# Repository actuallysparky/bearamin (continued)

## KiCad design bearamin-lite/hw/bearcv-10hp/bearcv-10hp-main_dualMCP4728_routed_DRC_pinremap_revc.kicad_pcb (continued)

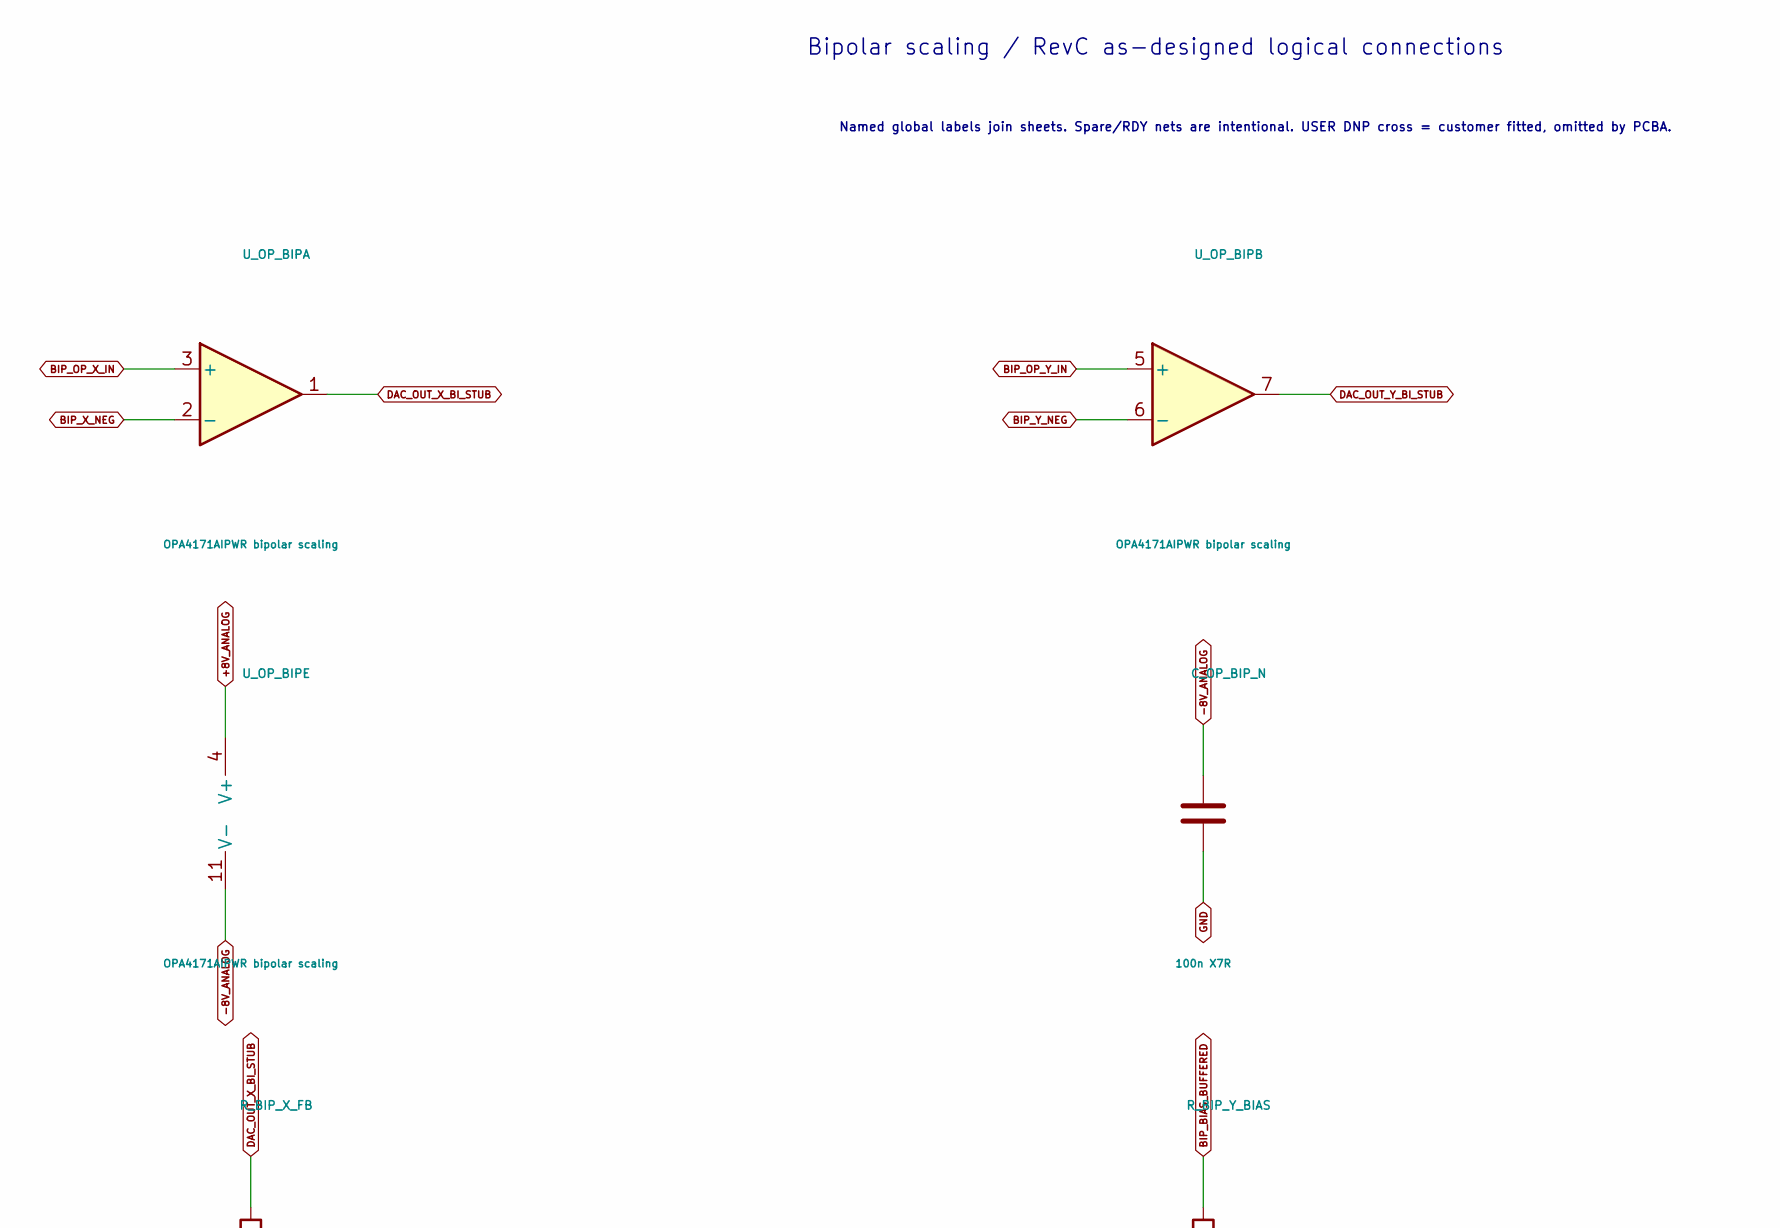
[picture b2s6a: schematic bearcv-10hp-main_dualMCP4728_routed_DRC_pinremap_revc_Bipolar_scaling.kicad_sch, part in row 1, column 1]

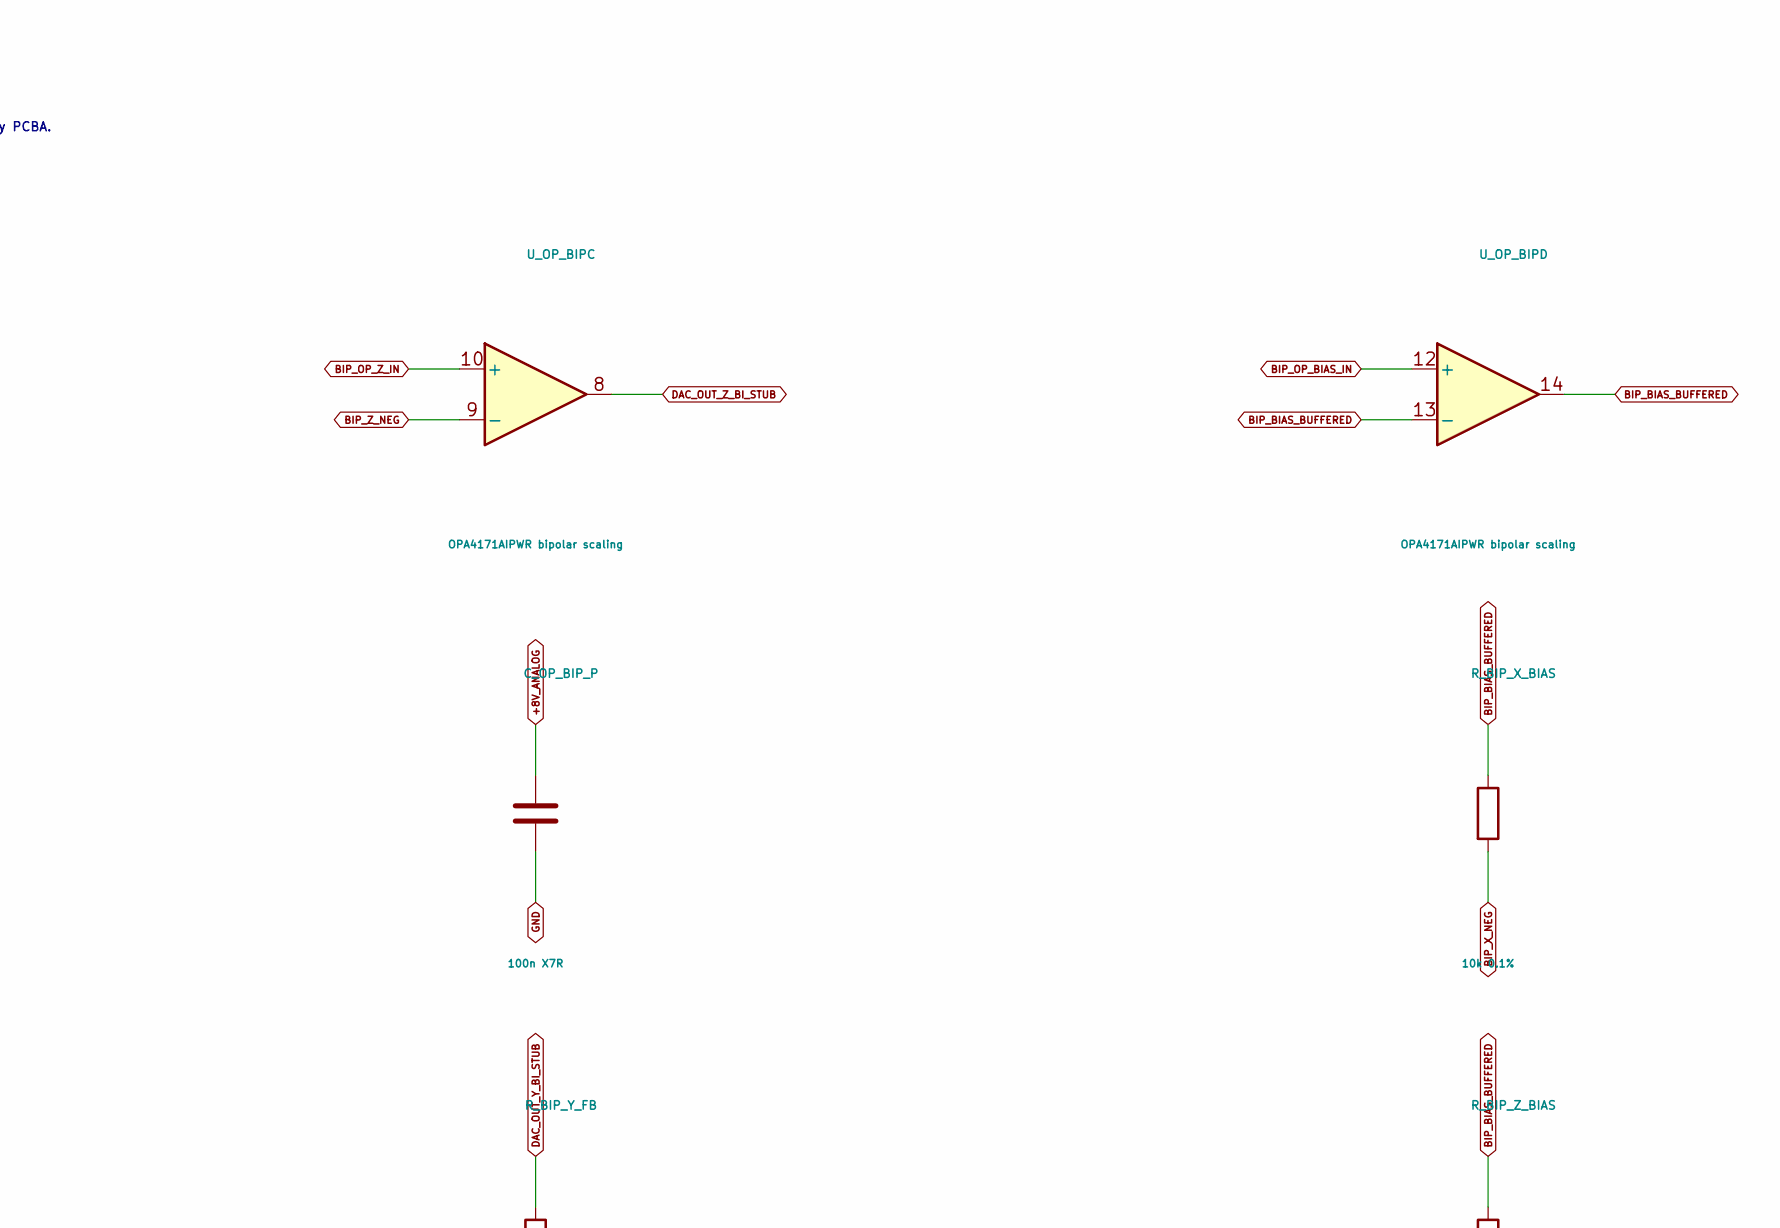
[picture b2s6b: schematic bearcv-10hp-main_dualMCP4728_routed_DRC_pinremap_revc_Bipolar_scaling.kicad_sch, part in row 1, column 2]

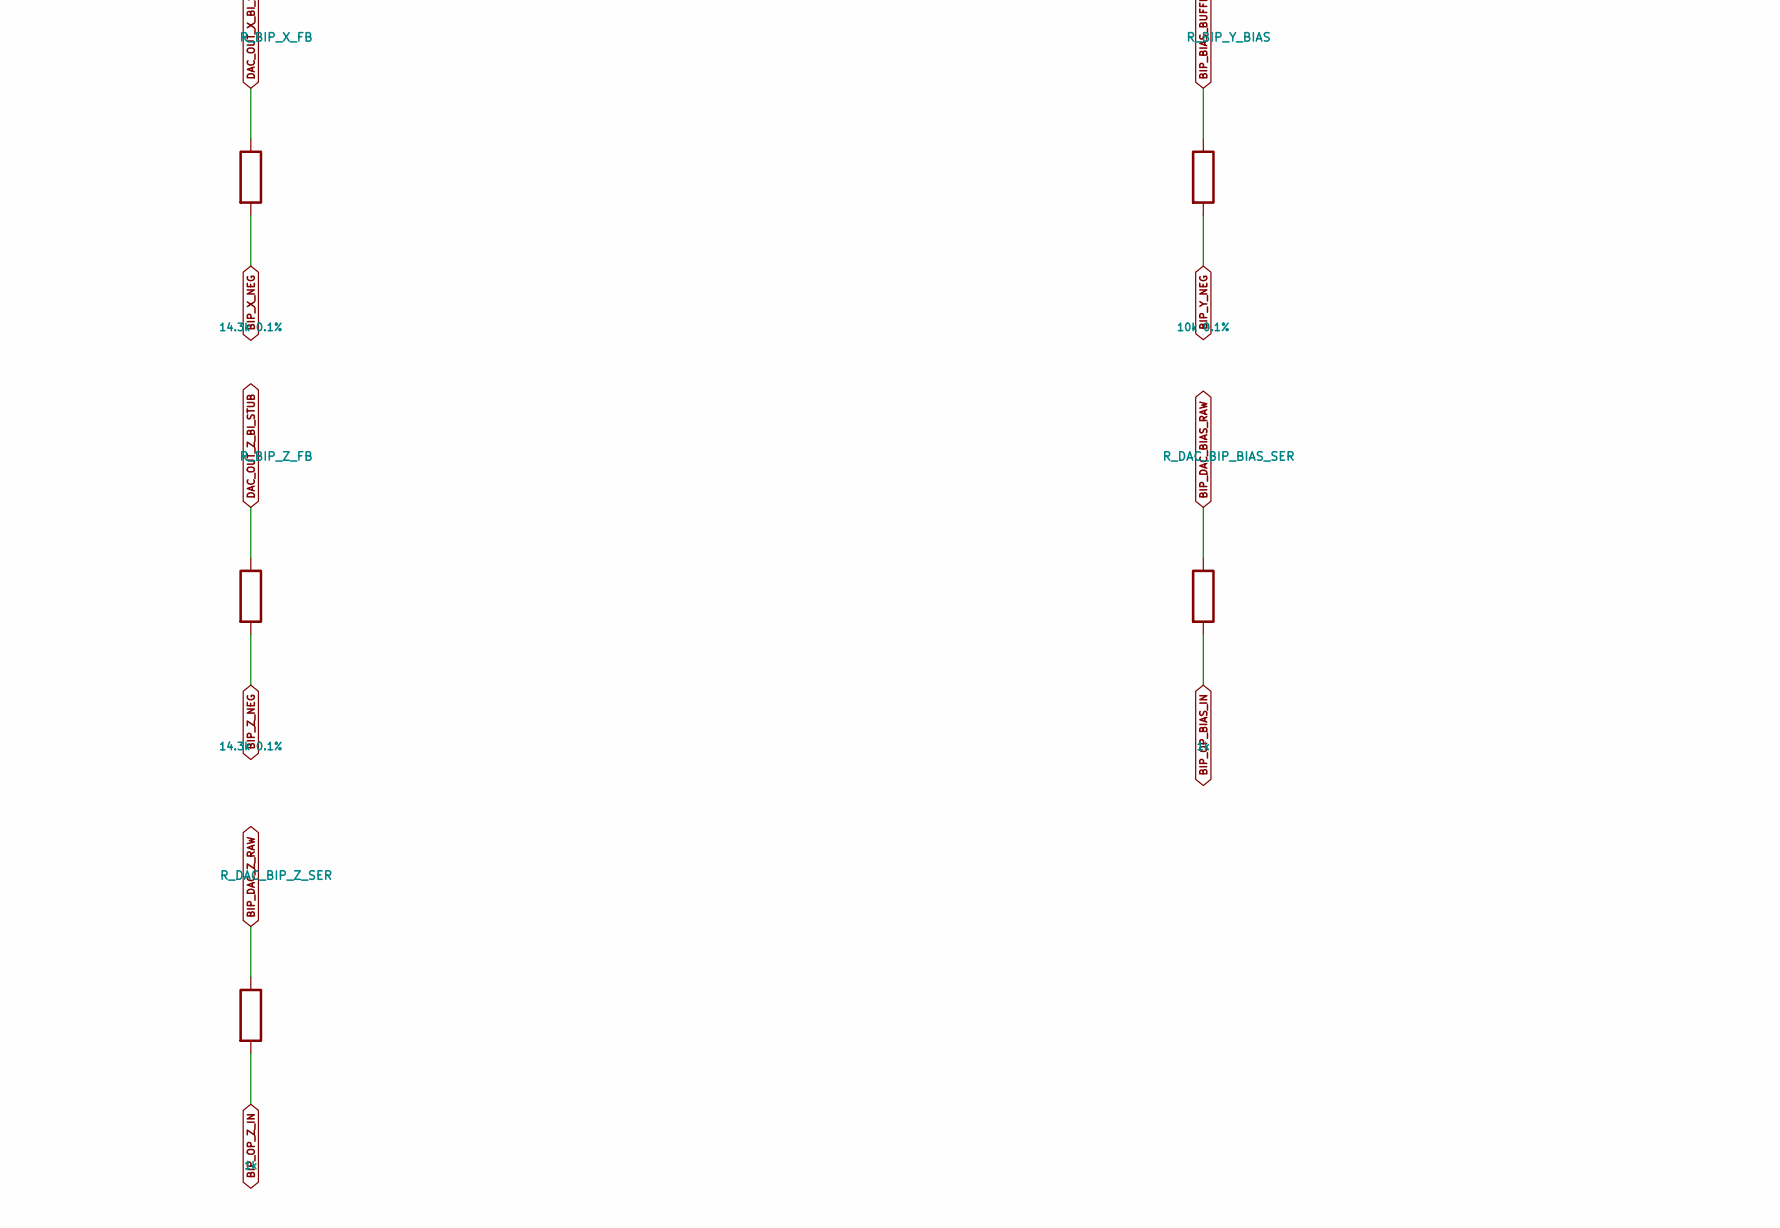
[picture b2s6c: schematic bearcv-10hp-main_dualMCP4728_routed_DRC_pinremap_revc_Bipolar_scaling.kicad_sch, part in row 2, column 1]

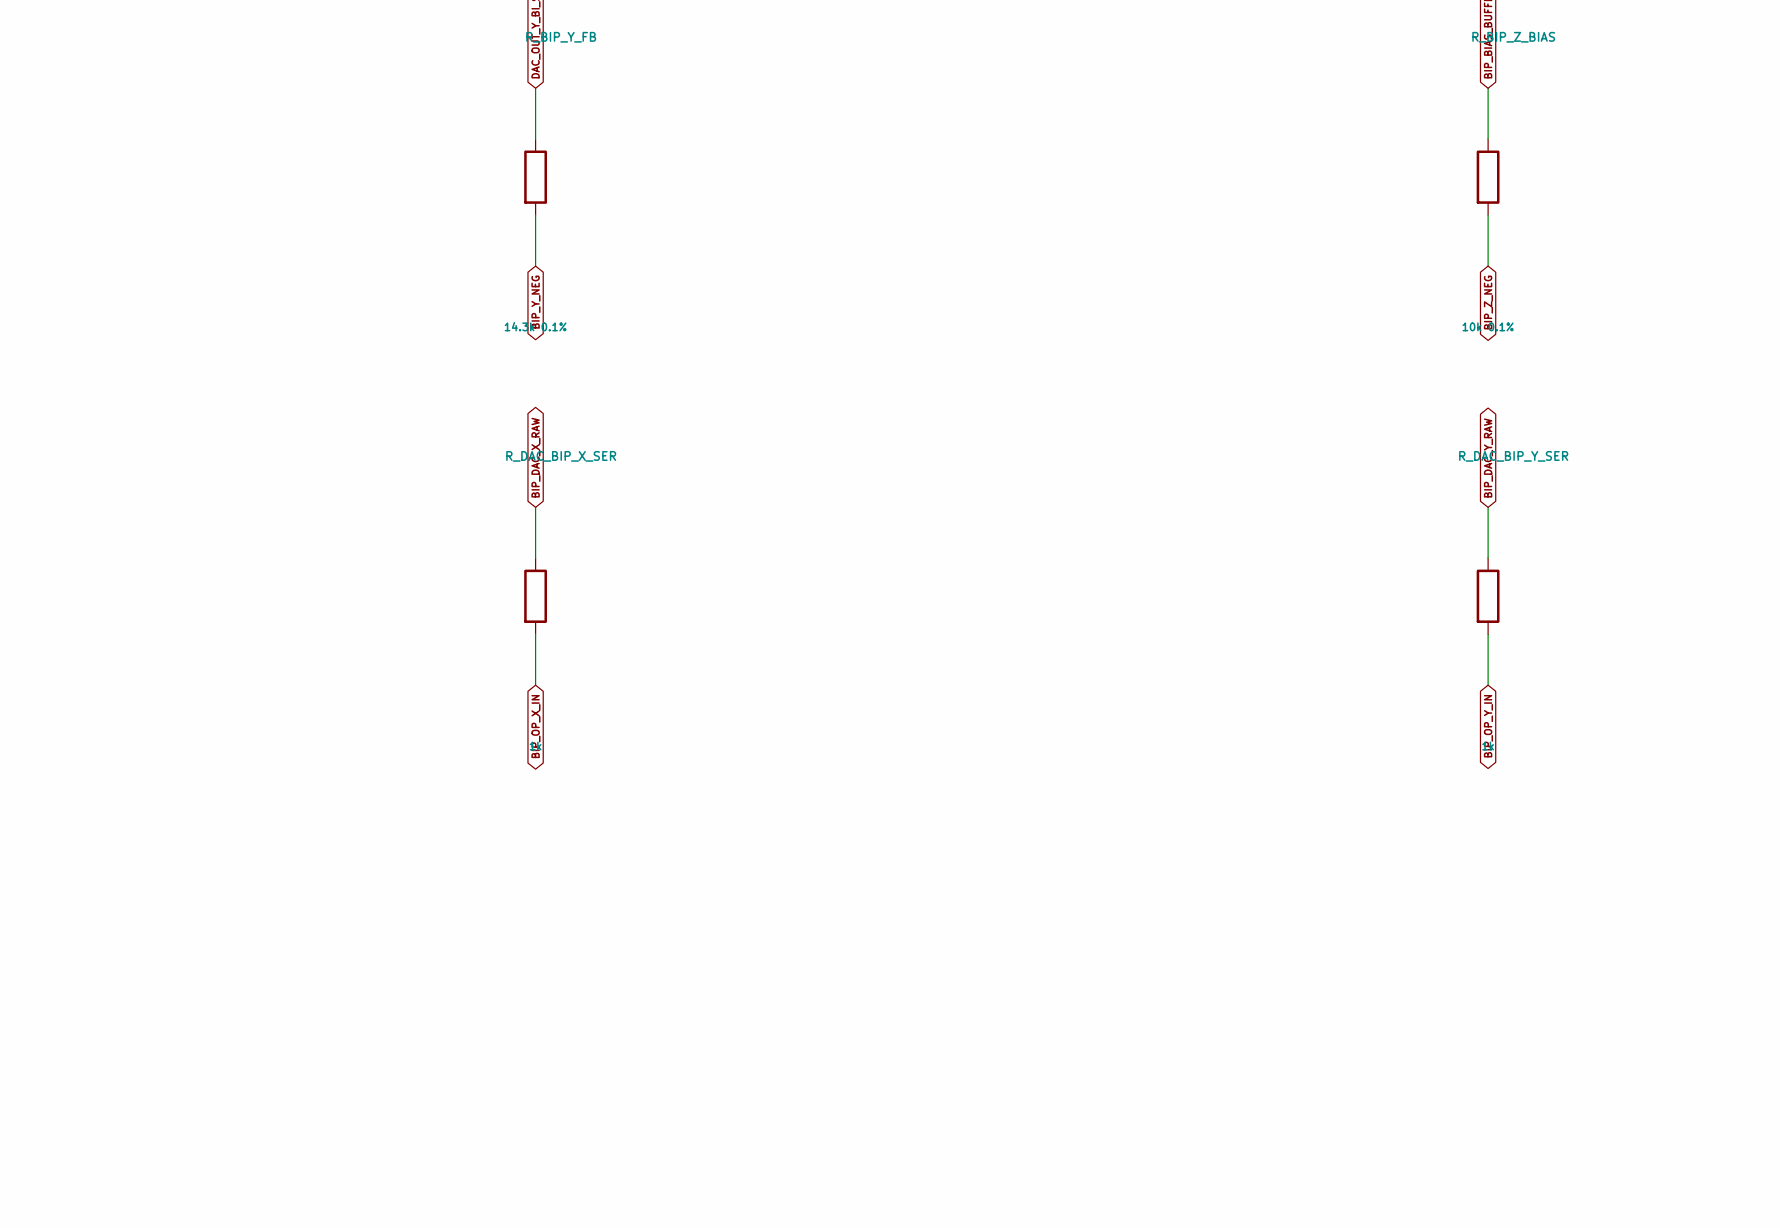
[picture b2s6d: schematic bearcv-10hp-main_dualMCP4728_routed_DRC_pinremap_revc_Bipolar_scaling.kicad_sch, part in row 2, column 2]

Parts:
C_OP_BIP_N: 100n X7R; MPN CC0603KRX7R9BB104; JLCPCB Part C14663
C_OP_BIP_P: 100n X7R; MPN CC0603KRX7R9BB104; JLCPCB Part C14663
R_BIP_X_BIAS: 10k 0.1%; MPN RT0603BRD0710KL; JLCPCB Library Extended
R_BIP_X_FB: 14.3k 0.1%; MPN RT0603BRE0714K3L; JLCPCB Library Extended
R_BIP_Y_BIAS: 10k 0.1%; MPN RT0603BRD0710KL; JLCPCB Library Extended
R_BIP_Y_FB: 14.3k 0.1%; MPN RT0603BRE0714K3L; JLCPCB Library Extended
R_BIP_Z_BIAS: 10k 0.1%; MPN RT0603BRD0710KL; JLCPCB Library Extended
R_BIP_Z_FB: 14.3k 0.1%; MPN RT0603BRE0714K3L; JLCPCB Library Extended
R_DAC_BIP_BIAS_SER: 1k; MPN 0603WAF1001T5E; JLCPCB Part C21190
R_DAC_BIP_X_SER: 1k; MPN 0603WAF1001T5E; JLCPCB Part C21190
R_DAC_BIP_Y_SER: 1k; MPN 0603WAF1001T5E; JLCPCB Part C21190
R_DAC_BIP_Z_SER: 1k; MPN 0603WAF1001T5E; JLCPCB Part C21190
U_OP_BIP: OPA4171AIPWR bipolar scaling; MPN OPA4171AIPWR; JLCPCB Part C529553

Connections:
+8V_ANALOG: C_OP_BIP_P.1, U_OP_BIP.4 (V+); also elsewhere on the board
-8V_ANALOG: C_OP_BIP_N.1, U_OP_BIP.11 (V-); also elsewhere on the board
BIP_BIAS_BUFFERED: R_BIP_X_BIAS.1, R_BIP_Y_BIAS.1, R_BIP_Z_BIAS.1, U_OP_BIP.13 (-), U_OP_BIP.14
BIP_DAC_BIAS_RAW: R_DAC_BIP_BIAS_SER.1; also elsewhere on the board
BIP_DAC_X_RAW: R_DAC_BIP_X_SER.1; also elsewhere on the board
BIP_DAC_Y_RAW: R_DAC_BIP_Y_SER.1; also elsewhere on the board
BIP_DAC_Z_RAW: R_DAC_BIP_Z_SER.1; also elsewhere on the board
BIP_OP_BIAS_IN: R_DAC_BIP_BIAS_SER.2, U_OP_BIP.12 (+)
BIP_OP_X_IN: R_DAC_BIP_X_SER.2, U_OP_BIP.3 (+)
BIP_OP_Y_IN: R_DAC_BIP_Y_SER.2, U_OP_BIP.5 (+)
BIP_OP_Z_IN: R_DAC_BIP_Z_SER.2, U_OP_BIP.10 (+)
BIP_X_NEG: R_BIP_X_BIAS.2, R_BIP_X_FB.2, U_OP_BIP.2 (-)
BIP_Y_NEG: R_BIP_Y_BIAS.2, R_BIP_Y_FB.2, U_OP_BIP.6 (-)
BIP_Z_NEG: R_BIP_Z_BIAS.2, R_BIP_Z_FB.2, U_OP_BIP.9 (-)
DAC_OUT_X_BI_STUB: R_BIP_X_FB.1, U_OP_BIP.1; also elsewhere on the board
DAC_OUT_Y_BI_STUB: R_BIP_Y_FB.1, U_OP_BIP.7; also elsewhere on the board
DAC_OUT_Z_BI_STUB: R_BIP_Z_FB.1, U_OP_BIP.8; also elsewhere on the board
GND: C_OP_BIP_N.2, C_OP_BIP_P.2; also elsewhere on the board

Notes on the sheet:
Bipolar scaling / RevC as-designed logical connections
Named global labels join sheets. Spare/RDY nets are intentional. USER DNP cross = customer fitted, omitted by PCBA.

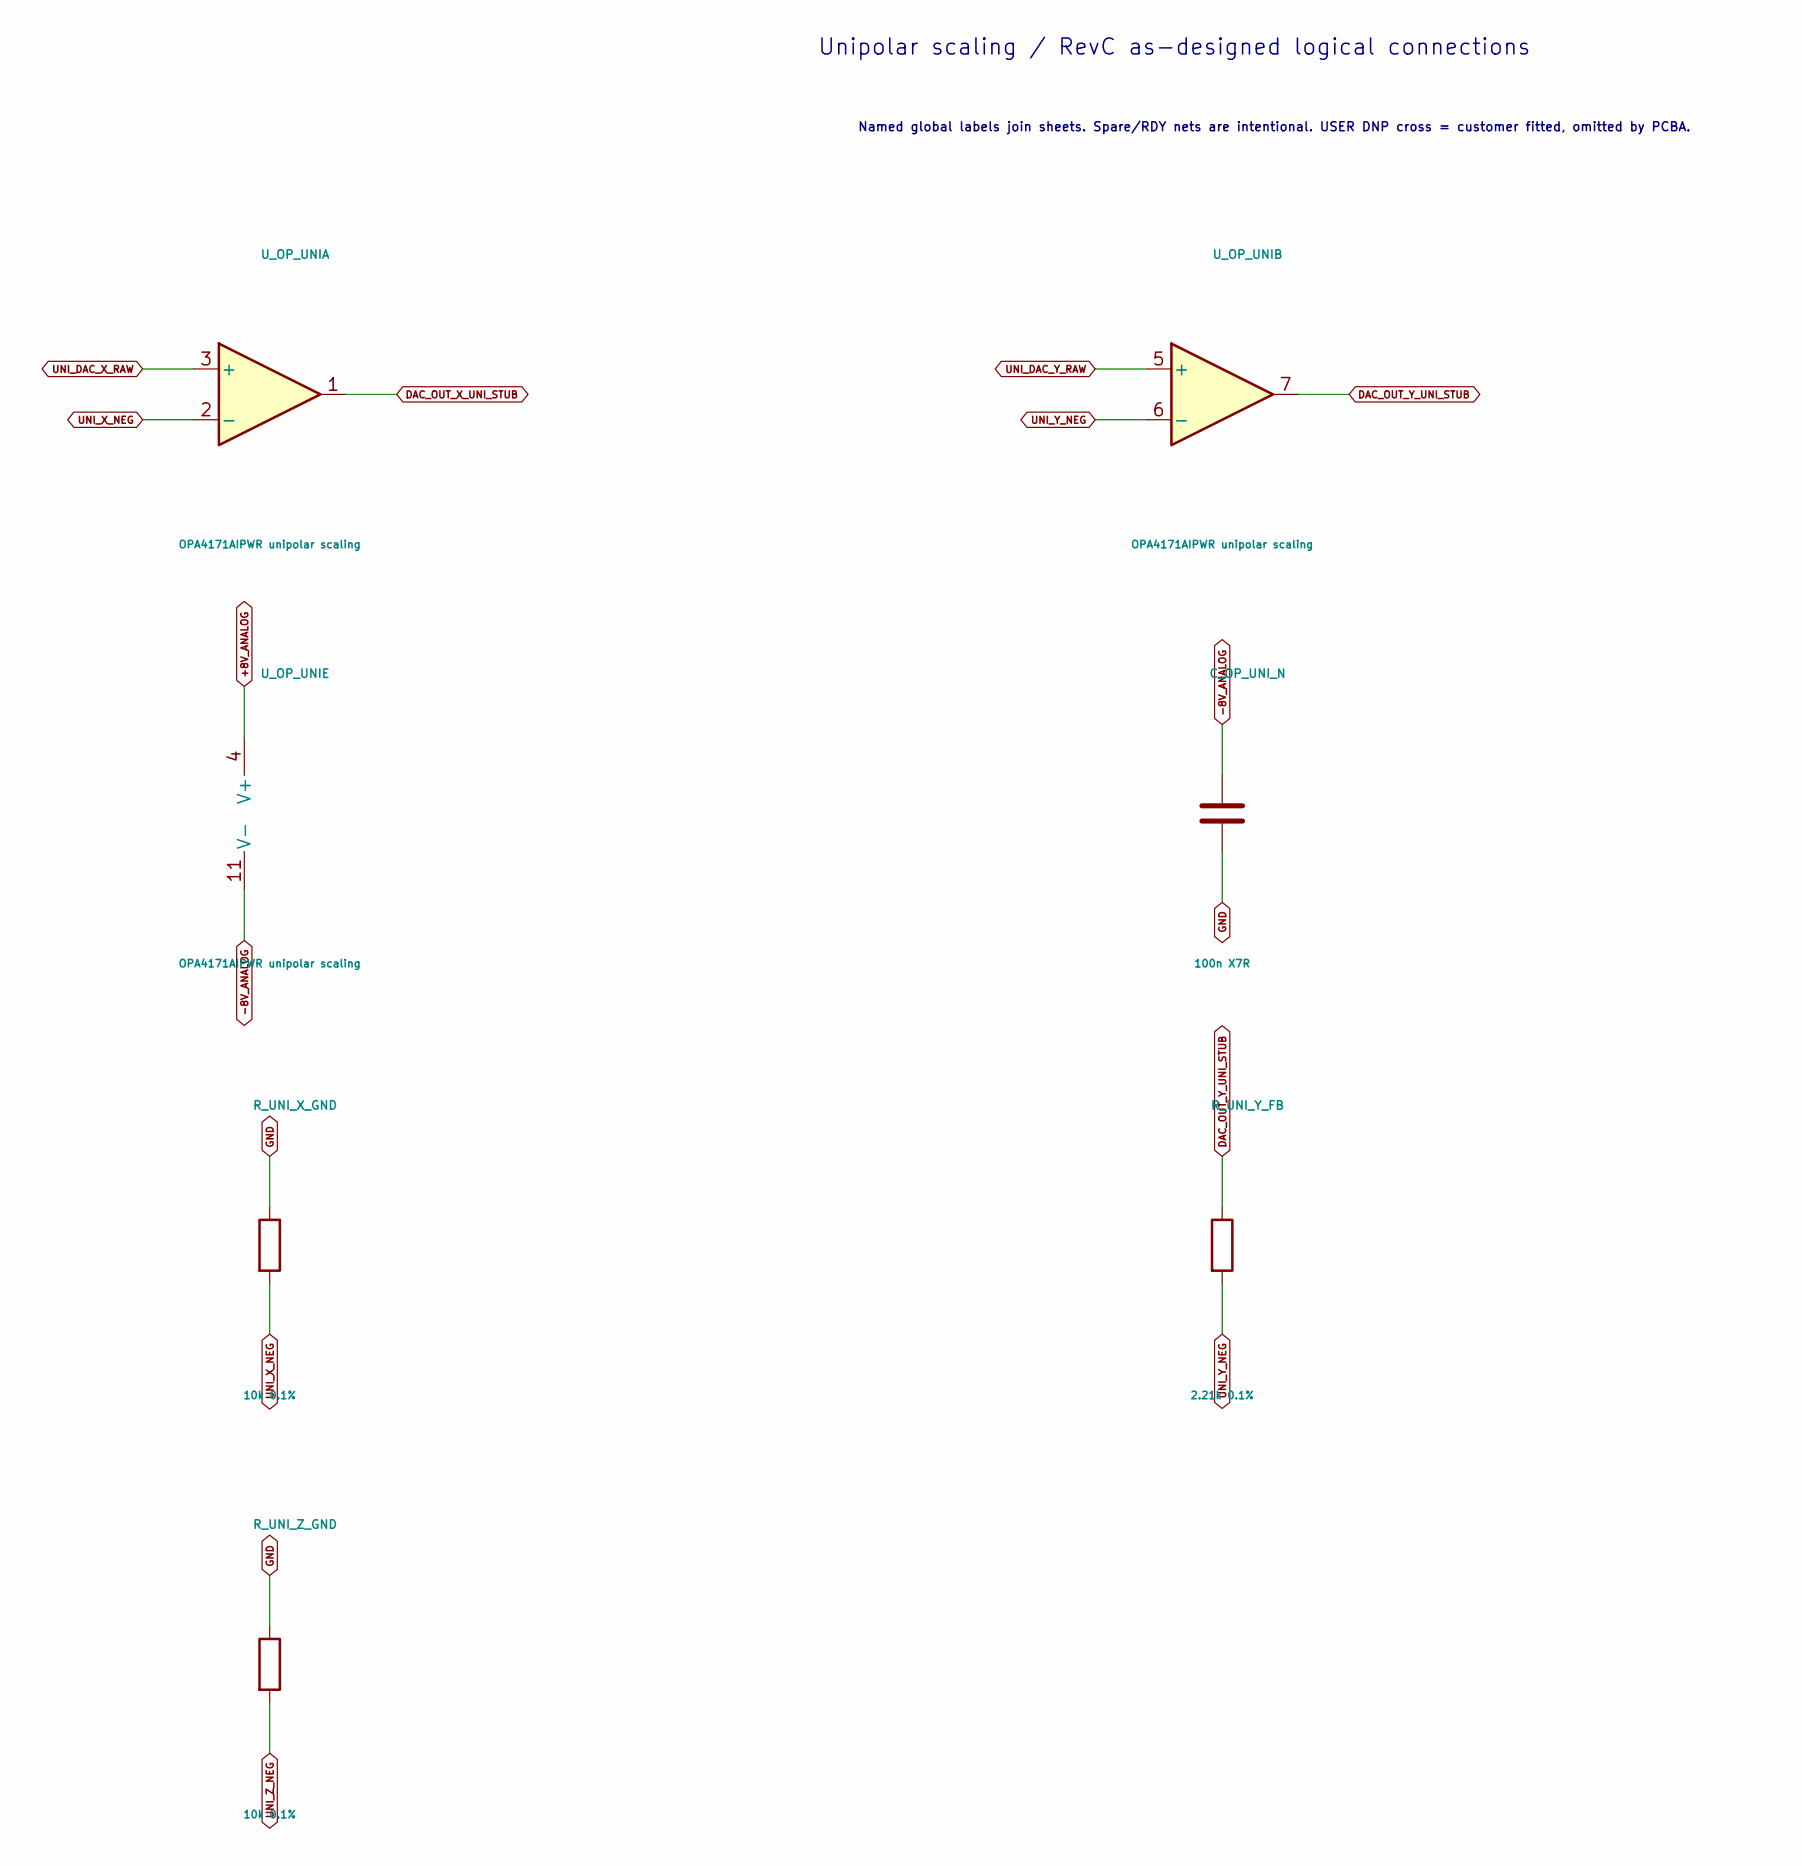
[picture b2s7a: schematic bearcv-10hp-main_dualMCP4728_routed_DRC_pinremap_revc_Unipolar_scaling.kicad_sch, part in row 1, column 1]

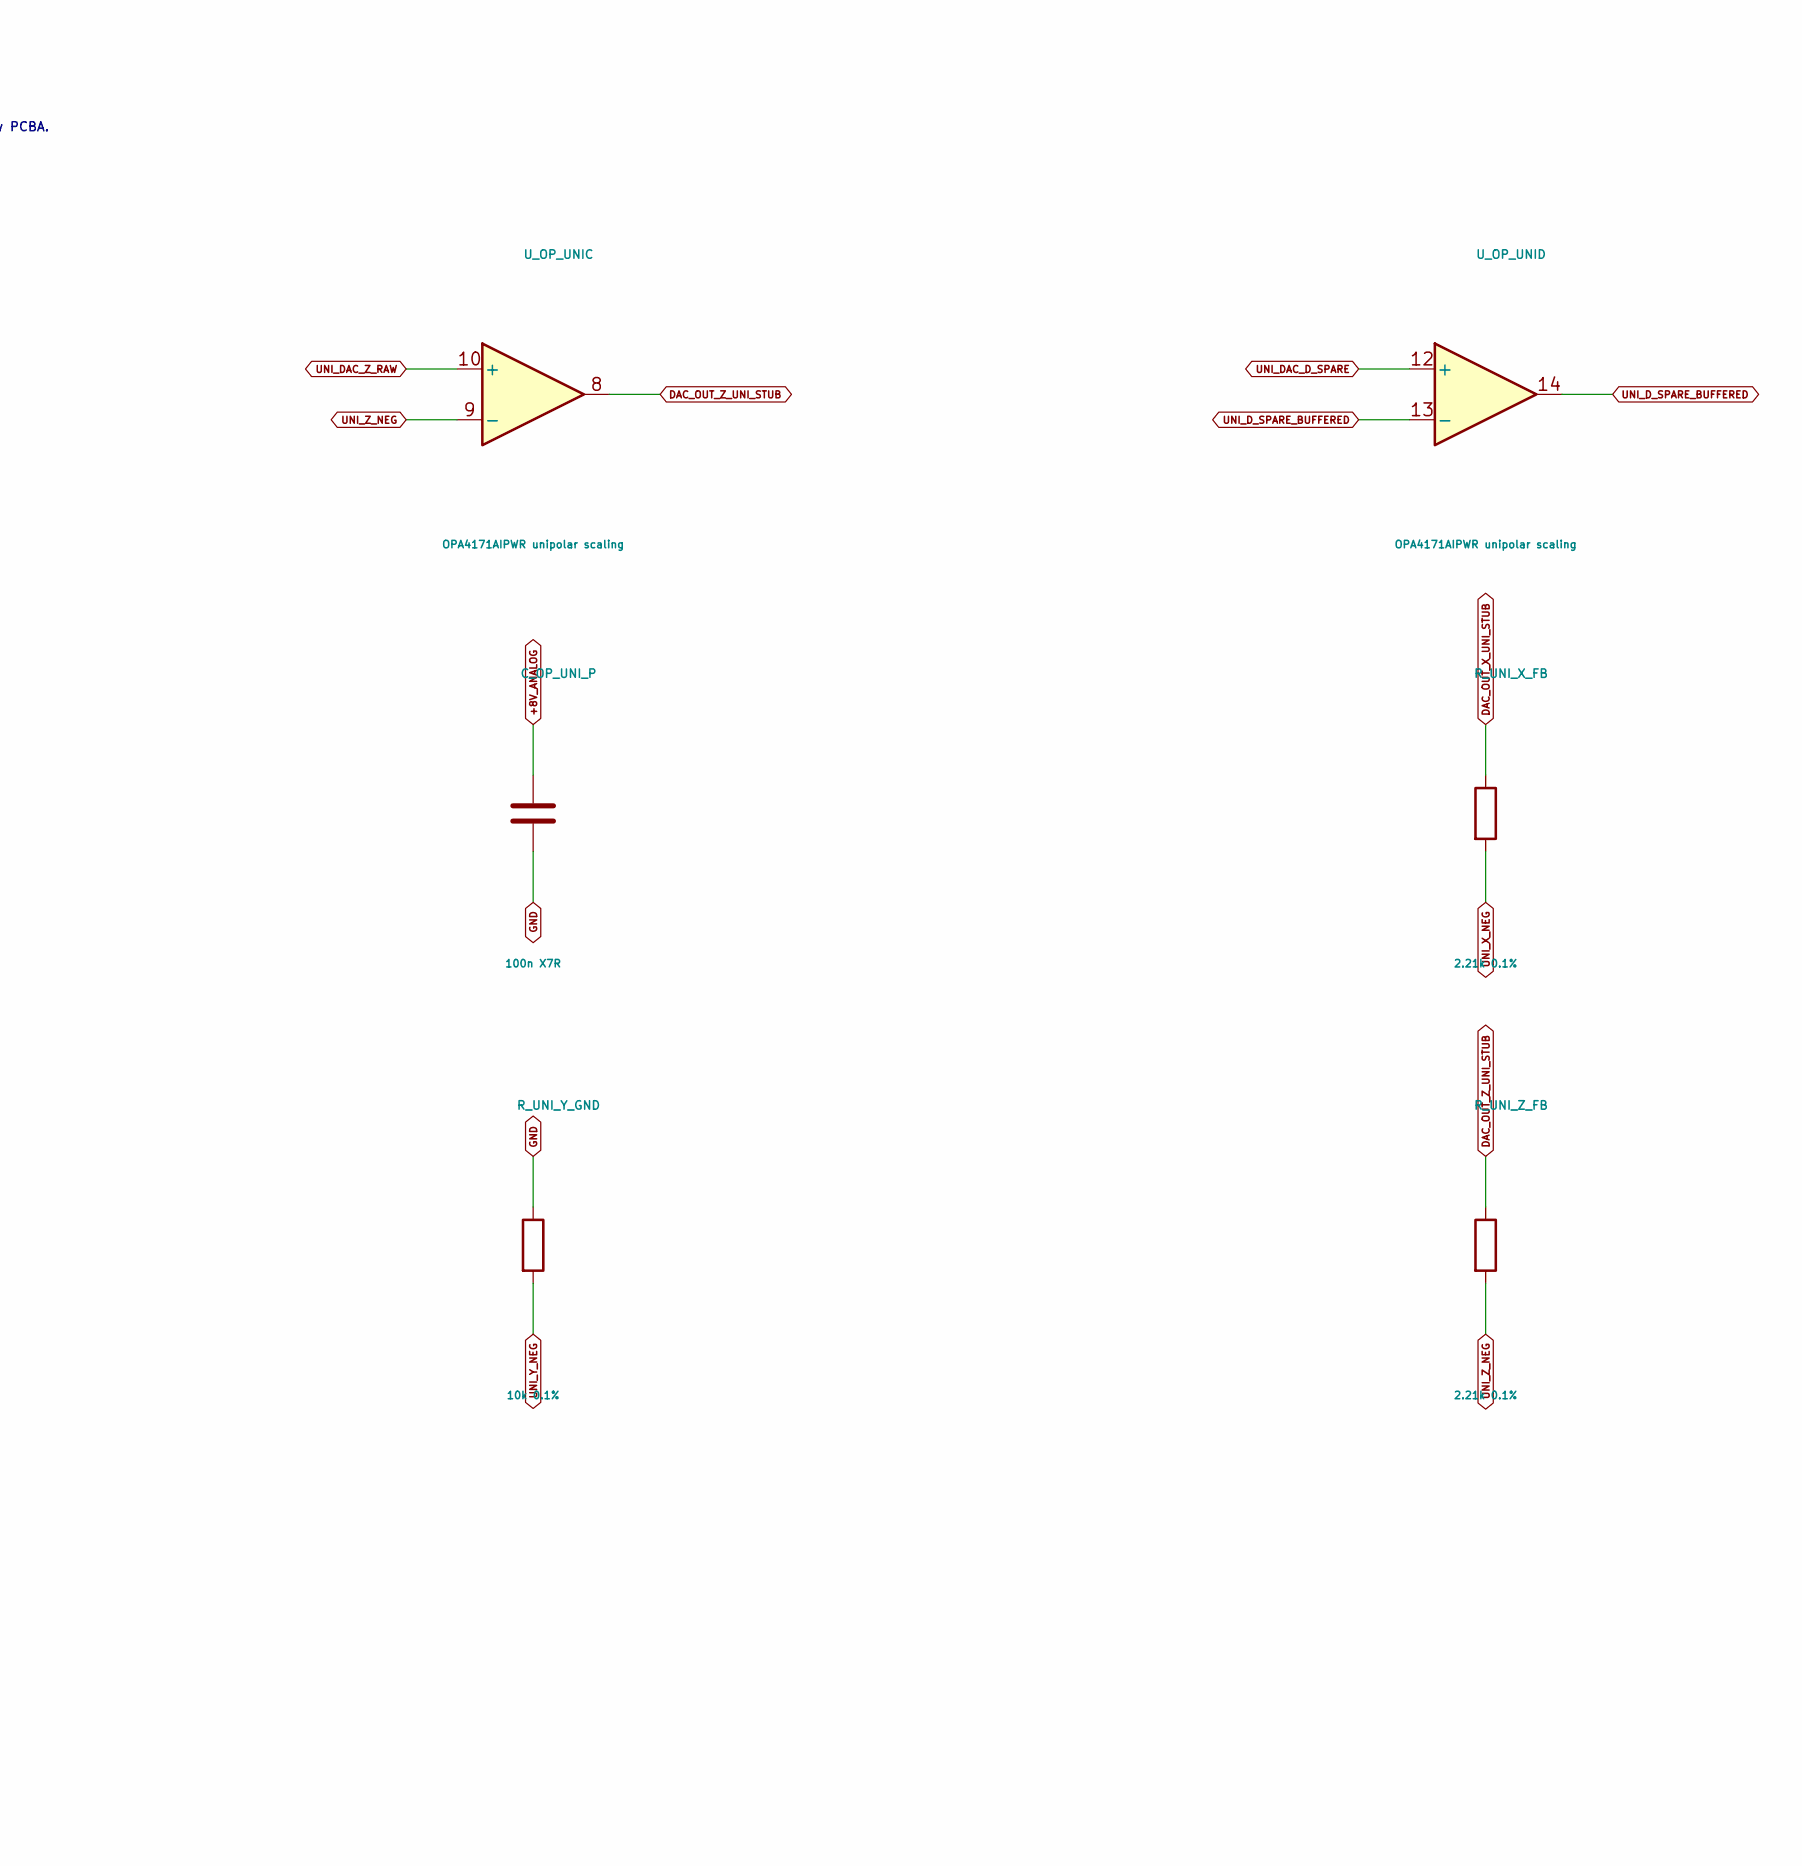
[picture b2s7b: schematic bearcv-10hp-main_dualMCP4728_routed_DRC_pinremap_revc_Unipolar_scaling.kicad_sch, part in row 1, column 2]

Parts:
C_OP_UNI_N: 100n X7R; MPN CC0603KRX7R9BB104; JLCPCB Part C14663
C_OP_UNI_P: 100n X7R; MPN CC0603KRX7R9BB104; JLCPCB Part C14663
R_UNI_X_FB: 2.21k 0.1%; MPN RT0603BRD072K21L; JLCPCB Library Extended
R_UNI_X_GND: 10k 0.1%; MPN RT0603BRD0710KL; JLCPCB Library Extended
R_UNI_Y_FB: 2.21k 0.1%; MPN RT0603BRD072K21L; JLCPCB Library Extended
R_UNI_Y_GND: 10k 0.1%; MPN RT0603BRD0710KL; JLCPCB Library Extended
R_UNI_Z_FB: 2.21k 0.1%; MPN RT0603BRD072K21L; JLCPCB Library Extended
R_UNI_Z_GND: 10k 0.1%; MPN RT0603BRD0710KL; JLCPCB Library Extended
U_OP_UNI: OPA4171AIPWR unipolar scaling; MPN OPA4171AIPWR; JLCPCB Part C529553

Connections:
+8V_ANALOG: C_OP_UNI_P.1, U_OP_UNI.4 (V+); also elsewhere on the board
-8V_ANALOG: C_OP_UNI_N.1, U_OP_UNI.11 (V-); also elsewhere on the board
DAC_OUT_X_UNI_STUB: R_UNI_X_FB.1, U_OP_UNI.1; also elsewhere on the board
DAC_OUT_Y_UNI_STUB: R_UNI_Y_FB.1, U_OP_UNI.7; also elsewhere on the board
DAC_OUT_Z_UNI_STUB: R_UNI_Z_FB.1, U_OP_UNI.8; also elsewhere on the board
GND: C_OP_UNI_N.2, C_OP_UNI_P.2, R_UNI_X_GND.1, R_UNI_Y_GND.1, R_UNI_Z_GND.1; also elsewhere on the board
UNI_DAC_D_SPARE: U_OP_UNI.12 (+); also elsewhere on the board
UNI_DAC_X_RAW: U_OP_UNI.3 (+); also elsewhere on the board
UNI_DAC_Y_RAW: U_OP_UNI.5 (+); also elsewhere on the board
UNI_DAC_Z_RAW: U_OP_UNI.10 (+); also elsewhere on the board
UNI_D_SPARE_BUFFERED: U_OP_UNI.13 (-), U_OP_UNI.14
UNI_X_NEG: R_UNI_X_FB.2, R_UNI_X_GND.2, U_OP_UNI.2 (-)
UNI_Y_NEG: R_UNI_Y_FB.2, R_UNI_Y_GND.2, U_OP_UNI.6 (-)
UNI_Z_NEG: R_UNI_Z_FB.2, R_UNI_Z_GND.2, U_OP_UNI.9 (-)

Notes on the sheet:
Unipolar scaling / RevC as-designed logical connections
Named global labels join sheets. Spare/RDY nets are intentional. USER DNP cross = customer fitted, omitted by PCBA.
